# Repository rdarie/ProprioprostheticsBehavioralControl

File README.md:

code for monkey behavioral control in the proprioprosthetics project.

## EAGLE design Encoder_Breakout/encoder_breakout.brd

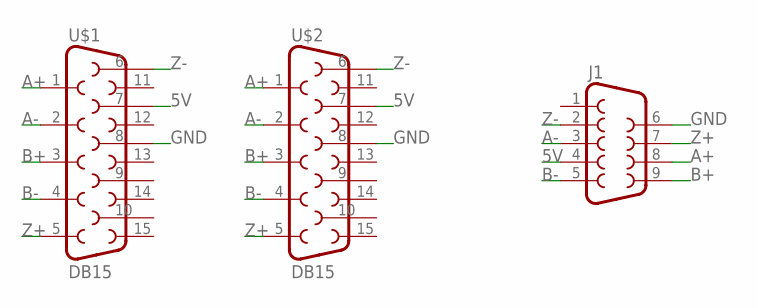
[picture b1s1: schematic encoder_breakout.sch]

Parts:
J1: DB9FEMALE; DB9
U$1, U$2: DB15

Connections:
5V: J1.4, U$1.7, U$2.7
A+: J1.8, U$1.1, U$2.1
A-: J1.3, U$1.2, U$2.2
B+: J1.9, U$1.3, U$2.3
B-: J1.5, U$1.4, U$2.4
GND: J1.6, U$1.8, U$2.8
Z+: J1.7, U$1.5, U$2.5
Z-: J1.2, U$1.6, U$2.6

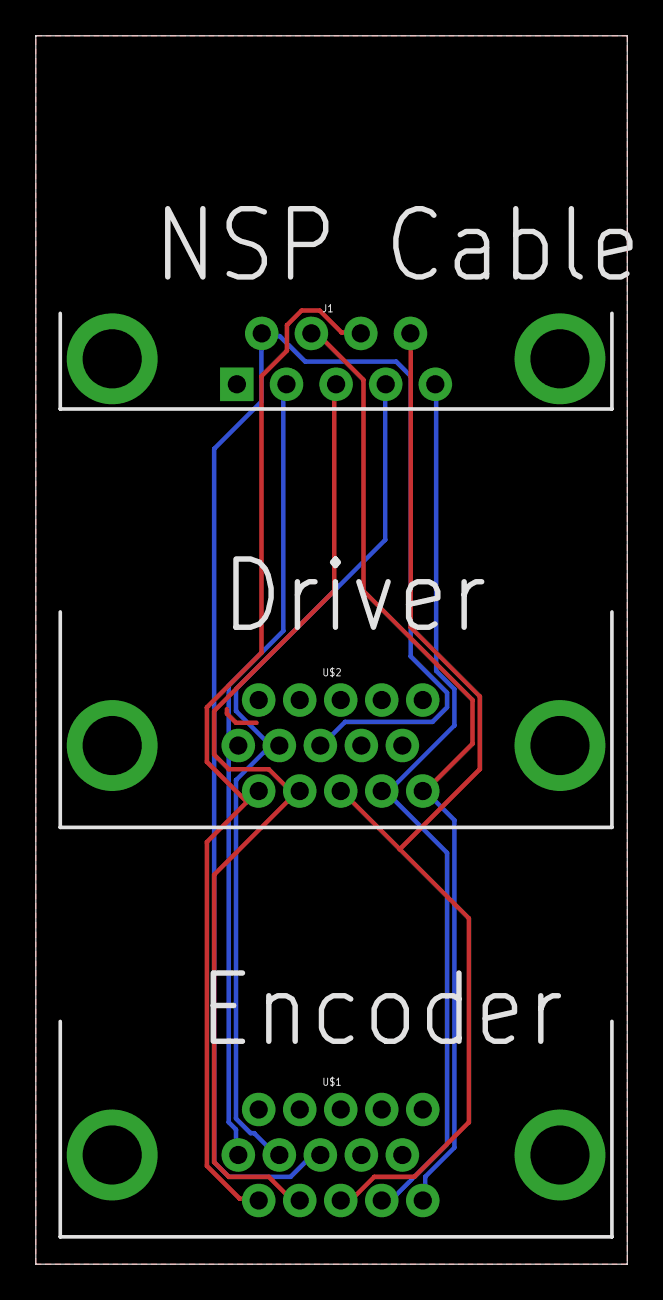
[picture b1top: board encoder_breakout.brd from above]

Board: 2 copper layers, 33.0 x 68.6 mm, 3 parts (0 on the bottom side), 8 nets.

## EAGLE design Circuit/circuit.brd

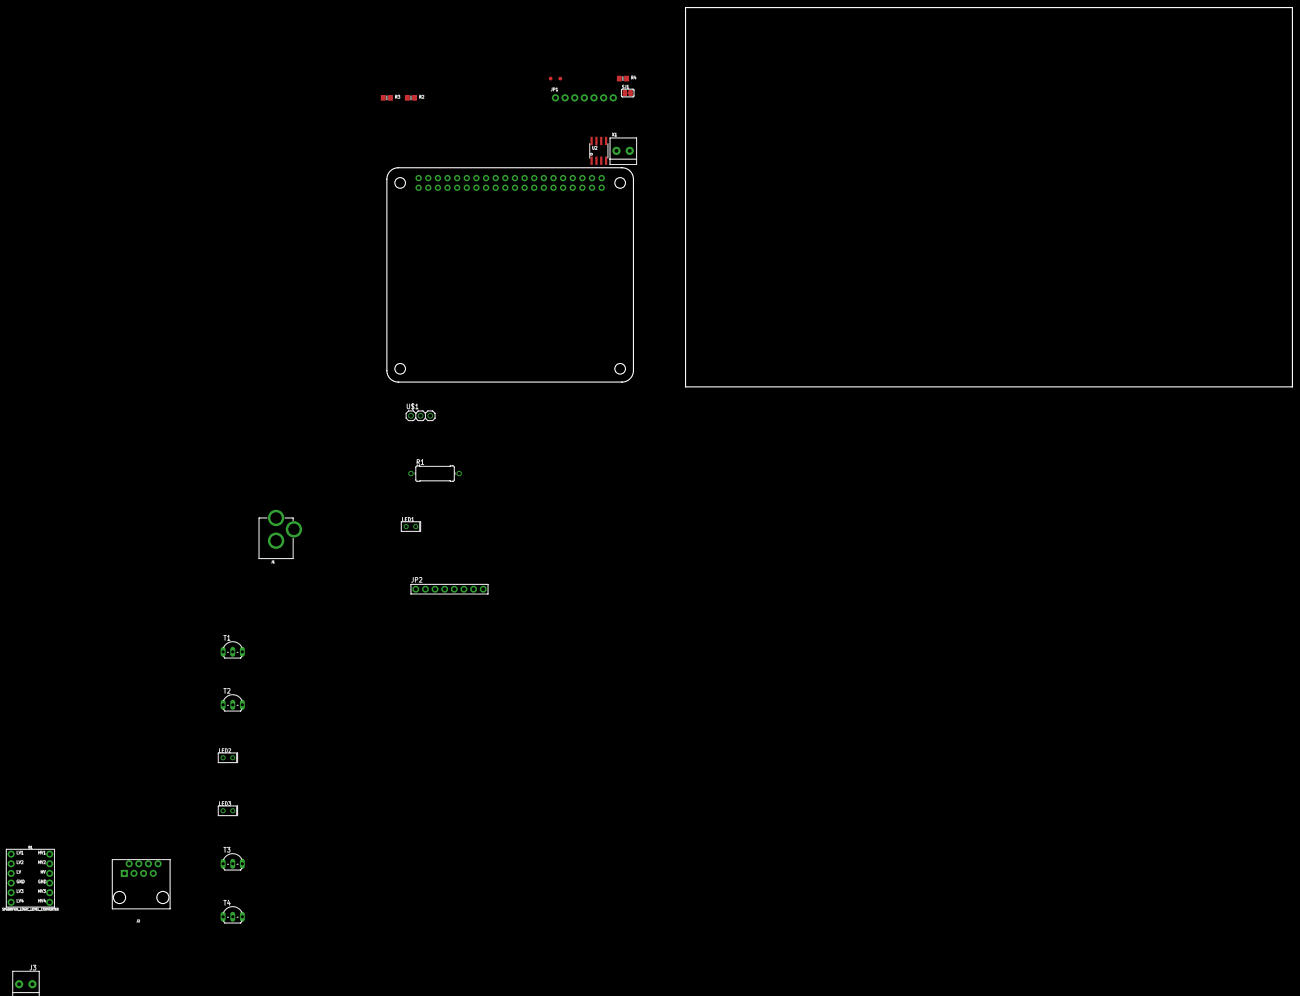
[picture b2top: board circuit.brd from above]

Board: 2 copper layers, 238.7 x 100.0 mm, 24 parts (0 on the bottom side), 25 nets, no tracks yet.

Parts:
B1: SPARKFUN_LOGIC_LEVEL_CONVERTER
FID3, FID4: FIDUCIAL""; FIDUCIAL_1MM
J1: POWER_JACK; POWER_JACK_PTH
J2: RJ45; RJ45-8
J3: 1X2-3.5MM
JP1: 1X07_ROUND_76
JP2: 1X08-BIG
LED1, LED2, LED3: LED2X5
R1: 0411/12
R2, R3, R4: 3.9K; 0805-NO
RPI1: RASPBERRYPI_BPLUS_HATNOSLOTS; PI_HAT_NOSLOTS
SJ1: WP; SOLDERJUMPER_CLOSEDWIRE
T1, T2, T3, T4: 2N2222; TO92-EBC-OVAL
U2: CAT24C32; SOIC8_150MIL
U$1: TSOP38238; 1X03
X1: TERMBLOCK_1X2-3.5MM

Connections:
3.3V: B1.LV, J2.6, J2.8, R2.2, R3.2, R4.2, RPI1.1, RPI1.17, U2.8, U$1.3
5.0V: JP1.1, RPI1.2, RPI1.4
12V: B1.HV, J1.PWR, J2.1, J2.3, LED2.A, LED3.A
BCLK: JP1.6, RPI1.12
BUT1: J2.5, RPI1.7
BUT2: J2.7, RPI1.11
CUE_1: B1.HV1, T1.B
CUE_2: B1.HV2, T2.B
CUE_BOTH: B1.HV3, T3.B, T4.B
DIN: JP1.5, RPI1.40
EECLK: R3.1, RPI1.28, U2.6
EEDATA: R2.1, RPI1.27, U2.5
GND: B1.GND1, B1.GND2, J3.2, JP1.2, LED1.K, RPI1.6, RPI1.9, RPI1.14, RPI1.20, RPI1.25, RPI1.30, RPI1.34, RPI1.39, SJ1.1, T1.E, T2.E, T3.E, T4.E, U2.1, U2.2, U2.3, U2.4, U$1.1
LED1: J2.2, LED3.K, T2.C, T3.C
LED1_CTRL: B1.LV1, RPI1.36
LED2: J2.4, LED2.K, T1.C, T4.C
LED2_CTRL: B1.LV2, RPI1.31
LED_BOTH_CTRL: B1.LV3, RPI1.32
LIRC_IN: RPI1.16, U$1.2
LRCLK: JP1.7, RPI1.35
unnamed: LED1.A, R1.2
unnamed: J1.GND, J1.GNDBREAK
unnamed: R4.1, SJ1.2, U2.7
PWR_LED: R1.1, RPI1.29
REWARD: J3.1, RPI1.22

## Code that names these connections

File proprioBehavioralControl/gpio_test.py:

import RPi.GPIO as GPIO
import time

BUT1 = 4
BUT2 = 17

LED1 = 16
LED2 = 6
LED_BOTH = 12

ctrl = {
    BUT1 : LED1,
    BUT2 : LED2
    }

status = {
    LED1 : False,
    LED2 : False,
    LED_BOTH : False
    }

def my_callback(channel):
    print('This is a edge event callback function!')
    print('Edge detected on channel %s'%channel)
    print('This is run in a different thread to your main program')
    status[ctrl[channel]] = not status[ctrl[channel]]
    GPIO.output(ctrl[channel], status[ctrl[channel]])

GPIO.setmode(GPIO.BCM) # Broadcom pin-numbering scheme

GPIO.setup(BUT1, GPIO.IN, pull_up_down = GPIO.PUD_DOWN) # Button pin set as input w/ pull-up
GPIO.setup(BUT2, GPIO.IN, pull_up_down = GPIO.PUD_DOWN) # Button pin set as input w/ pull-up

GPIO.setup(LED1, GPIO.OUT) # Button pin set as input w/ pull-up
GPIO.setup(LED2, GPIO.OUT) # Button pin set as input w/ pull-up
GPIO.setup(LED_BOTH, GPIO.OUT) # Button pin set as input w/ pull-up

GPIO.output(LED1, 0)
GPIO.output(LED2, 0)
GPIO.output(LED_BOTH, 0)

GPIO.add_event_detect(BUT1, GPIO.FALLING, callback=my_callback, bouncetime=200)  # add rising edge detection on a channel
GPIO.add_event_detect(BUT2, GPIO.FALLING, callback=my_callback, bouncetime=200)  # add rising edge detection on a channel

try:
    while 1:
        time.sleep(0.5)
        #status[LED_BOTH] = not status[LED_BOTH]
        #GPIO.output(LED_BOTH, status[LED_BOTH])
        status[LED1] = not status[LED1]
        GPIO.output(LED1, status[LED1])
        status[LED2] = not status[LED2]
        GPIO.output(LED2, status[LED2])

except KeyboardInterrupt: # If CTRL+C is pressed, exit cleanly:
    GPIO.cleanup() # cleanup all GPIO

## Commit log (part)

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2017-07-12 automation
2017-07-16 add LED lighting
2017-07-16 LED 2
2017-07-16 conditional logging
2017-07-16 revamp remote trainer
2017-07-16 fixes
2017-08-14 database upload
2017-08-14 add white noise
2017-08-14 tweak white noise voilume
2017-08-15 motor definition expanded
2017-08-15 tweak motor current
2017-08-15 started bad tone
2017-08-16 tweak step_3
2017-08-16 training_step_3 devel
2017-08-16 revamp game states a little bit
2017-08-16 debug step_3
2017-08-16 debugging
2017-08-16 game chamge
2017-08-17 stuff
2017-08-17 fixed first visit mechanism
2017-08-17 bug fixing
2017-08-17 bugfiex
2017-08-18 changing game_states.py
2017-08-18 add time out mechanism to game_states
2017-08-23 bugfixes
2017-08-23 bugfiexes
2017-08-23 bugfix
2017-09-06 compatibility fix
2017-09-08 louder for debug
2017-09-08 debug
2017-09-08 clean up so we can see
2017-09-08 fix me!
2017-09-25 made installable
2017-09-25 fix'
2017-09-25 Began working on stage 5
    ...
2017-09-28 stuff changed
2017-09-28 added difficult task
2017-09-28 difficulty tweak
2017-10-01 streamline data logging
2017-10-01 minor
2017-10-04 fixed error
2017-10-16 fixed gitignore issues
2017-10-16 evaluatePerformance syntax changed
2017-10-16 fixed gitigore bug
2017-10-17 switch to adafruit remote
2017-10-17 added incentive to press on hard trials
2017-10-17 made a note
2017-11-21 only easy to discriminate trials
2017-11-21 bugifx
2017-11-21 trial blocs
2017-11-21 added some variables to the google sheet log
2017-11-28 adding some temp files, should fix this at some point..
2017-12-01 adding per trial bloc lengths
2017-12-01 3 small throws, 7 long throws
2017-12-11 tweaked some rations
2017-12-11 added timeout during rotation and continuous block resizing
2017-12-11 merge
2017-12-11 added timeout for motor
2017-12-11 modified wait during motor movement code
2017-12-11 tweak to the wait enforcer
    made it so that it only waits after both rotation commands were sent
2017-12-11 append to previous
2017-12-11 fix above
2017-12-11 added logging of block length
2017-12-11 append
2017-12-11 added wait tone
2017-12-13 added wait to gitignore
2017-12-13 uncued now illuminates both
2017-12-15 more current
2017-12-15 stac6
2017-12-15 integer step size request
2017-12-18 changing block length
2017-12-18 changed velocity
2017-12-18 shorter blocs
2018-01-11 added some stuff
2018-01-11 found a bug in bloc length autotuning
2018-01-17 tweaked water
2018-01-17 fixed gitignore
2018-01-17 better bounds on block lengths
2018-01-17 gaussian block length
2018-01-18 reduced number of cue trials
2018-01-23 punishment timeout
2018-01-23 tweaked timeout
2018-01-31 fixed session timestamping to be month first
2018-02-01 motor speed optimization
2018-02-01 motor test
2018-02-01 add encoder feedback to motor
2018-02-04 encoder testing
2018-02-04 fixed merge
2018-02-04 motor testing
2018-02-08 shorter blocks
2018-02-09 faster and faster she goes
2018-02-09 made wrong timeout longer
2018-02-13 harder and harder it gets"
2018-02-13 harder!
2018-02-13 shortened wait timeout to reduce interval between stimulus and evaluation
2018-02-15 harder!!
2018-02-15 harder!!!
2018-02-15 shortened timing delays
2018-02-20 log json instead of tab delimited and sue the compound pedal move
2018-02-23 added harsher anti-bias rules
2018-02-26 close json log file
2018-02-26 removed trial start logging
    use wait for button instead, probably more realistic anyway
2018-02-26 fixed json logging even more
2018-02-26 reduce printing burden
    ...
2018-02-26 shorten!!!
2018-02-27 fixed naming inconsistency
2018-02-28 fixed logging
2018-03-01 added phantom throws
2018-03-01 Auto stash before merge of "master" and "origin/master"
2018-03-01 added wait for divider tone
2018-03-16 jackpot for switching between blocks
2018-03-16 fixed merge issue
2018-03-19 proprio step 1 rewrite
2018-03-21 updated lircrc
2018-03-21 added lircd
2018-03-21 button test scripte
2018-03-21 bla;
2018-03-21 changes to gpio-test
2018-03-21 added support for pi2 board
2018-03-23 added ble test
2018-03-23 using thalamus
2018-03-27 started work on predefined stimulus sets
2018-03-28 added discrimination target set
2018-03-28 longer long throw
2018-03-28 integrate sets of magnitudes
2018-03-28 tweak difficulty
2018-03-29 next steps
2018-04-03 increased step 11 difficulty
2018-04-05 startup_mailer must run on python 2
2018-04-06 added logging of stim pair
2018-04-06 fixed path issues
2018-04-09 debugging..
2018-04-09 finished debug
2018-04-22 added dummy smart pedals
2018-05-08 sync
2018-05-08 add virtually impossible condition
2018-05-08 fix block lengths
2018-05-23 step 14, BLE with fixed first throw
2018-05-24 stochastic reward schedule
2018-05-29 connect to pedal more often
2018-05-29 removed randomness of pedal vibromotor
2018-06-14 faster start
2018-07-17 minor changes
2018-07-17 adapted step counts to pedal rig 2.0
2018-09-20 new home position
2018-09-24 back to basics
2018-09-24 fixed left and right naming conventions
    fixed left and right naming conventions
2018-11-19 catching up with latest changes
2018-11-19 fixing merge issues...
2018-11-19 better resolution around perceptual threshold
2018-11-19 added variable Good game
2018-11-27 adding stuff
2018-11-27 changed units to 1/100 of a degree!
2018-11-27 added note about gearing
2019-01-07 added summit interface
2019-01-24 fixed bug due to misunderstanding of RLP program #
2019-01-28 added dummy motor to tasks with turn pedal and stim
2019-01-28 Update training_step_14_pi2.py
    ...
2020-04-26 add support for monopolar stim
2020-04-27 right before 20200427
2020-06-23 starting pi3 dev
2020-06-23 updated lirc API
2020-06-23 Update confAdafruit
2020-06-23 fixing lights
2020-06-24 updates to ripple controller
2020-06-24 commenting the automatic stim ripple code
2020-06-24 making high res stim
2020-06-29 added step 2
2020-06-30 06302020
2020-07-06 training_2
2020-07-07 HF block experiments
2020-08-04 fixed autocorrect function
2020-10-09 many changes to rippleControl
2020-10-13 migrating INS interface to this repo
2020-10-27 fix recording channels on summitPythonInterface
2020-10-27 folding minirc into python code
2021-01-13 debugging sheep json
2021-01-25 updating monkey scripts
2023-06-03 changed readme

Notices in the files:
parts and their libraries:
microbuilder: This work is placed in the public domain, and may be freely used for commercial and non-commercial work with the following conditions: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
SparkFun-Connectors: Licensing: Creative Commons ShareAlike 4.0 International - https://creativecommons.org/licenses/by-sa/4.0
